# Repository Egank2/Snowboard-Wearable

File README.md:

# 🏂 Snowboard Wearable – IoT-Based Ride Tracker

Welcome to the Snowboard Wearable project repository! This system is designed to help snowboarders visualize, analyze, and improve their performance using a wearable IoT device and a companion mobile application. It combines real-time sensor data, Bluetooth connectivity, trick recognition, and a gamified mobile UI for a next-generation snowboarding experience.

---

## 📱 Mobile App Features

- 🌤 **Weather & Conditions Dashboard** (Live resort data)
- 🏔 **Popular Resorts** listing with status
- 🔋 **Equipment Status Monitor** (Device, goggles, bindings)
- 🏆 **Leaderboards** (Daily, Weekly, Monthly, All-Time)
- 📊 **Trick Analytics** (Top speed, airtime, spins)
- 🕹 **3D Playback** of runs with XP scoring
- 👤 **User Profile & Stats** (XP, badges, levels)

Built using **Flutter**, supports Android 10+ and iOS 14+.

---

## ⚙️ Hardware Features

- 🎯 **ESP32-WROVER Module** for BLE and onboard control
- 🧭 **BNO086 IMU Sensor** for 9-axis motion tracking
- 🔌 **USB-C Charging** with Li-ion battery management
- 📉 **Low-Dropout Regulator (LDO)** for power efficiency
- 🧩 Designed and simulated in **KiCad 7.0**

---

## 🧪 Current Development Status

| Component            | Status            |
|----------------------|-------------------|
| Mobile UI            | ✅ In Progress     |
| ESP32 Firmware       | ✅ Completed     |
| IMU Integration      | ✅ Completed       |
| Trick Recognition ML | ✅ In Progress        |
| Cloud Sync & Storage | 🔄 Planned         |
| Hardware Prototype   | ✅ Assembled       |
| Full Integration     | ❌ Not Completed   |

---

## 🔧 Getting Started

### 📱 Mobile App (Swift)

### ⚡ Firmware (ESP32)

- Board: `ESP32-WROVER-E`
- Upload via USB using PlatformIO or Arduino IDE
- Ensure I²C is connected to the IMU (BNO086) with proper pull-ups

## 🧑‍💻 Team 06 — WIT COMP4960

- Emerson Herrera  
- Kenneth Egan
- Aakash Mukherjee 
- David Kennet  
- Victor Lomba  
Instructor: Dr. Joshua Gyllinsky

---

## 📘 Documentation

- [📄 SRS – Software Requirements Spec](Documents/SRS(Version%201.5).pdf)
- [📄 SDD – Software Design Document](Documents/SDD(Version%201.4).pdf)

---

## 🤝 Contributions

Pull requests are welcome! For major changes, please open an issue first to discuss what you'd like to change.  
Please follow our [Code of Conduct](docs/CODE_OF_CONDUCT.md).

---

## 📜 License

This project is intended for academic and research use only.
All rights reserved. Unauthorized use, reproduction, or distribution is prohibited.

---

## 🏔️ Let's Ride.

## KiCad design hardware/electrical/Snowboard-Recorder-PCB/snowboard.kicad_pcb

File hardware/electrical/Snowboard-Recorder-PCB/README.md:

# Snowboard-Recorder-PCB
Snowboard performance tracking PCB.

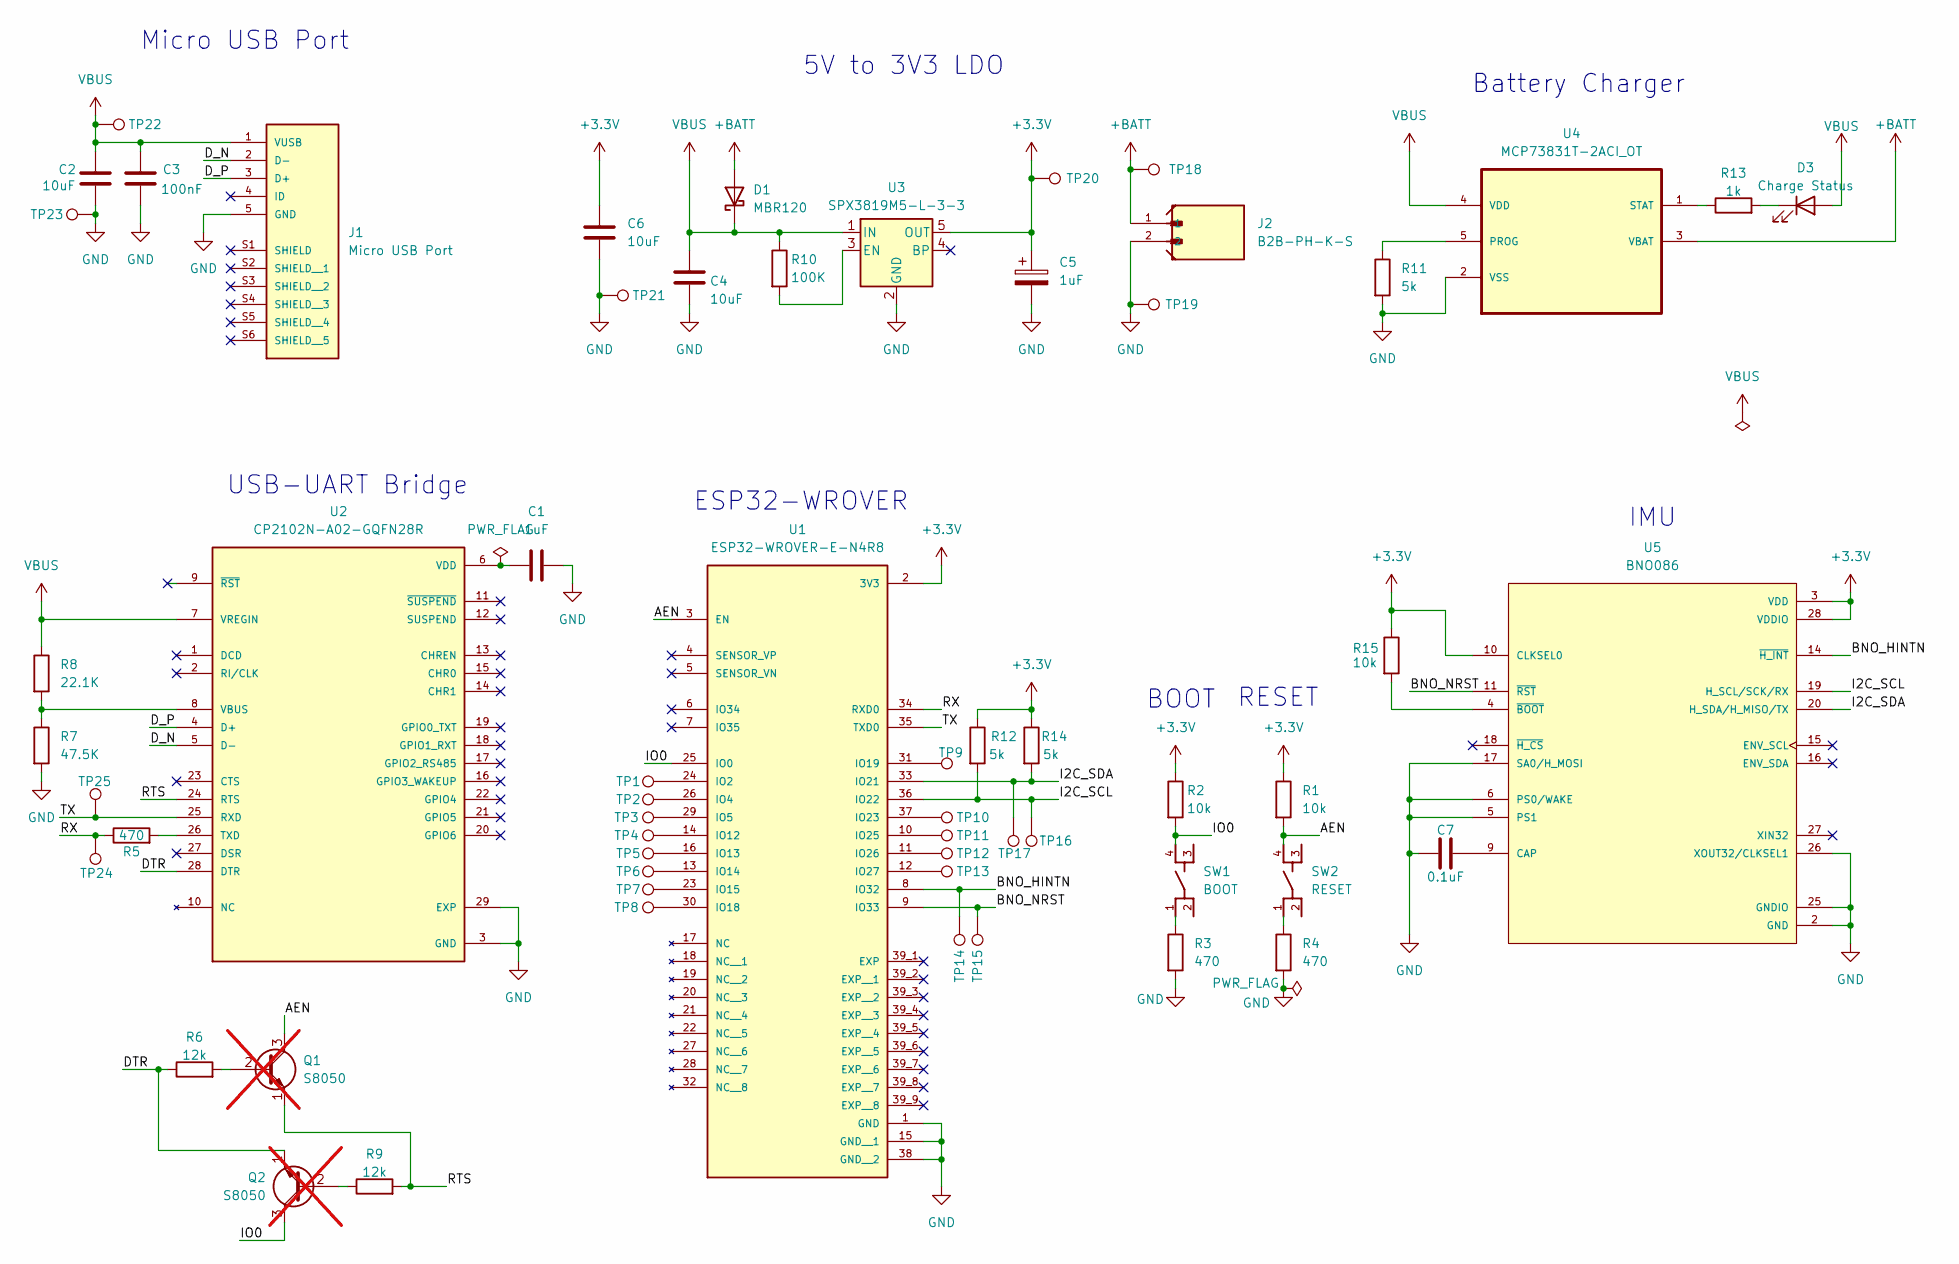
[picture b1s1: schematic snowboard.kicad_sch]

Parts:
C1, C5: 1uF
C2, C4, C6: 10uF
C3: 100nF
C7: 0.1uF
D1: MBR120
D3: Charge Status
J1: Micro USB Port; AMPHENOL_10118193-0001LF; PARTREV E
J2: B2B-PH-K-S; JST_B2B-PH-K-S
Q1, Q2: S8050; TO-92_Inline; not fitted
R1, R2, R15: 10k
R3, R4, R5: 470
R6, R9: 12k
R7: 47.5K
R8: 22.1K
R10: 100K
R11, R12, R14: 5k
R13: 1k
SW1: BOOT; SW_PTS810_SJM_250_SMTR_LFS
SW2: RESET; SW_PTS810_SJM_250_SMTR_LFS
TP1, TP2, TP3, TP4, TP5, TP6, TP7, TP8, TP9, TP10, TP11, TP12, TP13, TP14, TP15, TP16, TP17, TP18, TP19, TP20, TP21, TP22, TP23, TP24, TP25: TestPoint
U1: ESP32-WROVER-E-N4R8; XCVR_ESP32-WROVER-E-N4R8; PARTREV 1.6
U2: CP2102N-A02-GQFN28R; IC_CP2102N-A02-GQFN28R; PARTREV 1.5
U3: SPX3819M5-L-3-3; SOT-23-5
U4: MCP73831T-2ACI_OT; SOT95P280X145-5N; MPN MCP73831T-2ACI/OT
U5: BNO086; IC_BNO080; PARTREV 1.6

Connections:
+3.3V: C5.1, C6.1, R1.1, R2.1, R12.1, R14.1, R15.1, TP20.1, U1.2 (3V3), U3.5 (OUT), U5.3 (VDD), U5.10 (CLKSEL0), U5.28 (VDDIO)
+BATT: D1.2 (A), J2.1, TP18.1, U4.3 (VBAT)
/AEN: Q1.3 (C), R1.2, SW2.4, U1.3 (EN)
/BNO_HINTN: TP14.1, U1.8 (IO32), U5.14 (~H_INT)
/BNO_NRST: TP15.1, U1.9 (IO33), U5.11 (~RST)
/DTR: Q2.1 (E), R6.1, U2.28 (DTR)
/D_N: J1.2 (D-), U2.5 (D-)
/D_P: J1.3 (D+), U2.4 (D+)
/I2C_SCL: R12.2, TP16.1, U1.36 (IO22), U5.19 (H_SCL/SCK/RX)
/I2C_SDA: R14.2, TP17.1, U1.33 (IO21), U5.20 (H_SDA/H_MISO/TX)
/IO0: Q2.3 (C), R2.2, SW1.4, U1.25 (IO0)
/RTS: Q1.1 (E), R9.2, U2.24 (RTS)
/RX: R5.1, TP24.1, U1.34 (RXD0)
/TX: TP25.1, U1.35 (TXD0), U2.25 (RXD)
GND: C1.2, C2.2, C3.2, C4.2, C5.2, C6.2, C7.1, J1.5 (GND), J2.2, R3.2, R4.2, R7.2, R11.2, TP19.1, TP21.1, TP23.1, U1.1 (GND), U1.15 (GND__1), U1.38 (GND__2), U2.3 (GND), U2.29 (EXP), U3.2 (GND), U4.2 (VSS), U5.2 (GND), U5.5 (PS1), U5.6 (PS0/WAKE), U5.17 (SA0/H_MOSI), U5.25 (GNDIO), U5.26 (XOUT32/CLKSEL1)
unnamed: D3.1 (K), R13.2
unnamed: Q1.2 (B), R6.2
unnamed: Q2.2 (B), R9.1
unnamed: R3.1, SW1.1
unnamed: R4.1, SW2.1
unnamed: TP1.1, U1.24 (IO2)
unnamed: TP2.1, U1.26 (IO4)
unnamed: TP3.1, U1.29 (IO5)
unnamed: TP4.1, U1.14 (IO12)
unnamed: TP5.1, U1.16 (IO13)
unnamed: TP6.1, U1.13 (IO14)
unnamed: TP7.1, U1.23 (IO15)
unnamed: TP8.1, U1.30 (IO18)
unnamed: TP9.1, U1.31 (IO19)
unnamed: TP10.1, U1.37 (IO23)
unnamed: TP11.1, U1.10 (IO25)
unnamed: TP12.1, U1.11 (IO26)
unnamed: TP13.1, U1.12 (IO27)
unnamed: R5.2, U2.26 (TXD)
unnamed: R7.1, R8.2, U2.8 (VBUS)
unnamed: C1.1, U2.6 (VDD)
unnamed: R10.2, U3.3 (EN)
unnamed: R11.1, U4.5 (PROG)
unnamed: R13.1, U4.1 (STAT)
unnamed: C7.2, U5.9 (CAP)
unnamed: R15.2, U5.4 (~BOOT)
VBUS: C2.1, C3.1, C4.1, D1.1 (K), D3.2 (A), J1.1 (VUSB), R8.1, R10.1, TP22.1, U2.7 (VREGIN), U3.1 (IN), U4.4 (VDD)

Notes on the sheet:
USB-UART Bridge
IMU
Battery Charger
Micro USB Port
ESP32-WROVER
RESET
5V to 3V3 LDO
BOOT

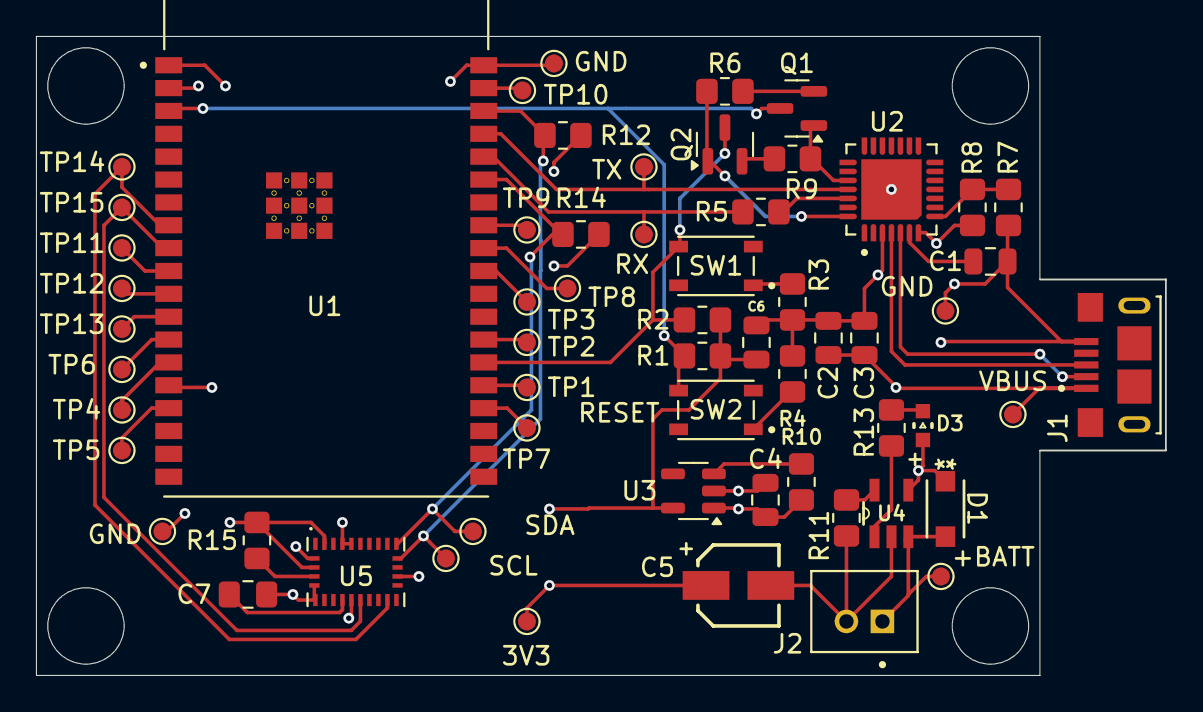
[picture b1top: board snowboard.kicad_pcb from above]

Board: 4 copper layers, 62.7 x 35.5 mm, 60 parts (0 on the bottom side), 42 nets.

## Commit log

2025-04-12 Add hardware sources
2025-04-14 interesting code
2025-04-14 Add runs and edited algorithms
2025-04-15 Add visualizer
2025-04-15 Add trick recognition
2025-04-15 Add Readme's and other files
